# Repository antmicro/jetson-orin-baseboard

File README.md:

# Antmicro Baseboard for Jetson Orin

Copyright (c) 2022-2026 [Antmicro](https://www.antmicro.com)

## Overview

This project contains open hardware design files for a baseboard supporting [NVIDIA Jetson Orin series](https://www.nvidia.com/en-us/autonomous-machines/embedded-systems/jetson-orin/) of System on Modules (SoMs) including Jetson Orin NX and Jetson Orin Nano.
The board break-routes the typical I/O interfaces from the SoM.
Additionally, it exposes an expansion connector which allows it to be integrated with external processing modules using USB, PCIe or low-speed interfaces.

The design files were prepared in KiCad 9.x.

## Key features

* Two USB PD ports
* DC Power connector
* MIPI CSI-2 interfaces on 50-pin connectors with configurable lane mapping
* Micro HDMI connector
* USB-C 10 Gbps with USB PD and DP
* USB-C 10 Gbps
* USB-C UART with USB PD
* M.2 key M
* M.2 key E
* 1Gb Ethernet with PoE
* Custom expansion connector
* RTC battery backup

## Project structure

The main directory contains KiCad PCB project files, a LICENSE, and a README.
The remaining files are stored in the following directories:

* `img` - contains graphics for this README
* `doc` - contains [documentation and usage instructions](https://antmicro.github.io/jetson-orin-baseboard)

The board exposes MIPI CSI-2 interfaces using unified 50-pin connectors that are electrically compatible with a variety of video accessories created by Antmicro:

* [GMSL Deserializer](https://github.com/antmicro/gmsl-deserializer)
* [SDI-MIPI Video converter](https://github.com/antmicro/sdi-mipi-video-converter)
* [HDMI-MIPI bridge](https://github.com/antmicro/hdmi-mipi-bridge)
* [CVBS-MIPI bridge](https://github.com/antmicro/cvbs-mipi-bridge)
* [OV5640 Dual camera board](https://github.com/antmicro/ov5640-dual-camera-board)
* [OV9281 Dual camera board](https://github.com/antmicro/ov9281-camera-board)
* [Storage Expansion board](https://github.com/antmicro/job-storage-expansion)
* [FRAMOS camera adapter](https://github.com/antmicro/framos-csi-adapter)
* [Allied Vision Alvium Camera Adapter](https://github.com/antmicro/alvium-flexible-csi-adapter)

## Licensing

This project is published under the [Apache-2.0](LICENSE) license.

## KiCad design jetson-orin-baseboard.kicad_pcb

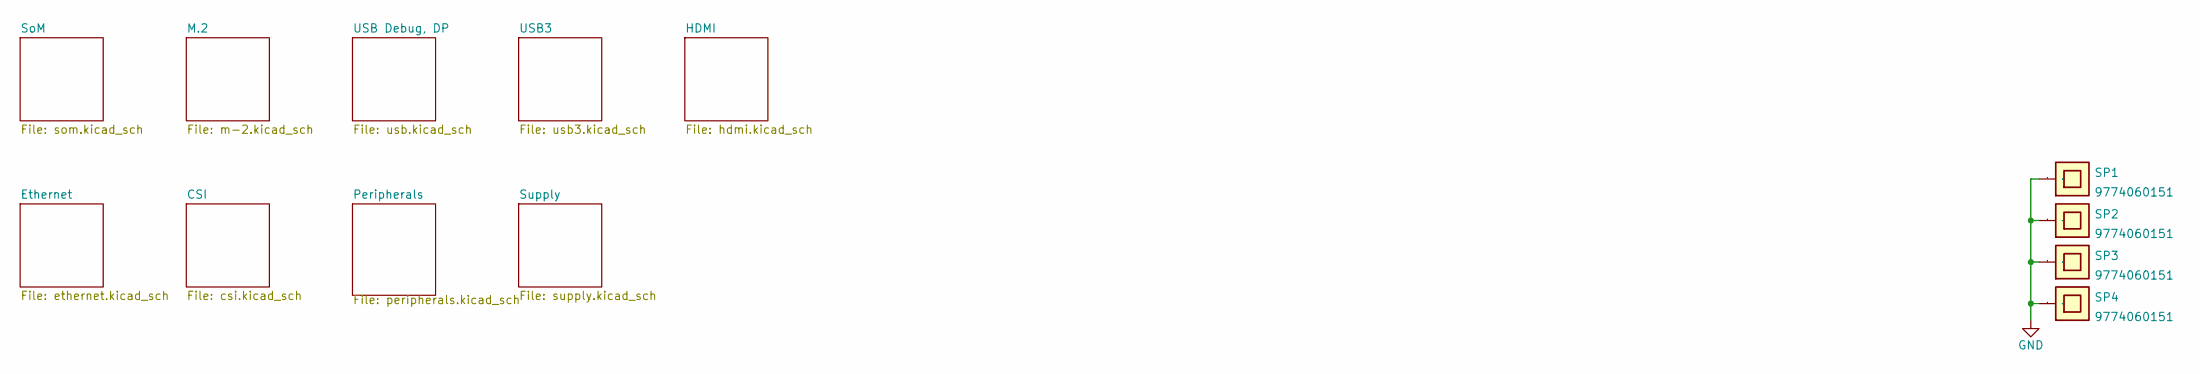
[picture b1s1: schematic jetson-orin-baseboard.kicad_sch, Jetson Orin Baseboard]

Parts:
SP1, SP2, SP3, SP4: 9774060151; MPN 9774060151

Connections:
GND: SP1.1, SP2.1, SP3.1, SP4.1; also elsewhere on the board

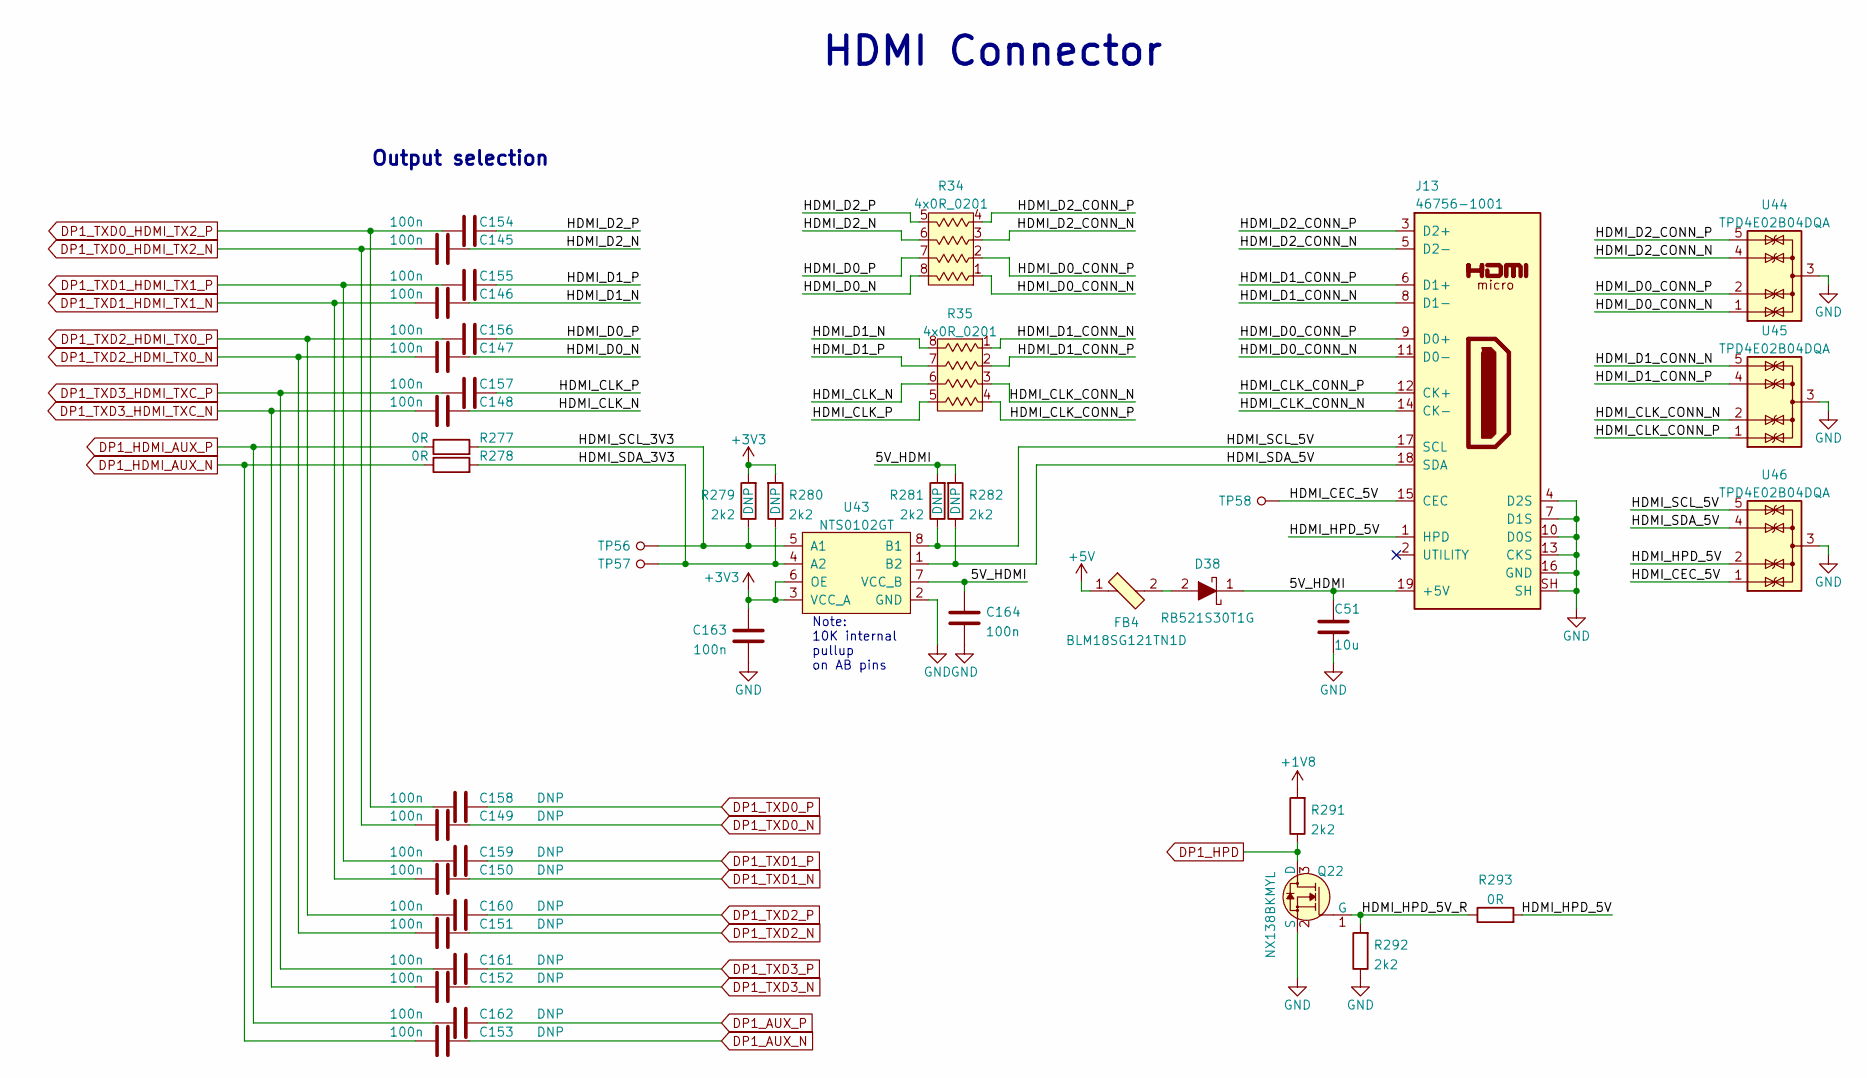
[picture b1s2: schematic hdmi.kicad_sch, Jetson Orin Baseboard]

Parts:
C51: C_10u_0603; 0603-cap; MPN GRM188R61A106KE69D
C145, C146, C147, C148, C149, C150, C151, C152, C153, C154, C155, C156, C157, C158, C159, C160, C161, C162, C163, C164: C_100n_0402; 0402-cap; MPN GRM155R61H104KE14D
D38: RB521S30T1G; SOD-523; MPN RB521S30T1G
FB4: BLM18SG121TN1D; 0603-res; MPN BLM18SG121TN1D
J13: 46756-1001; HDMI_Micro-D_Molex_46765-1x01; MPN 467651001
Q22: NX138BKMYL; DFN1006-3; MPN NX138BKMYL
R34, R35: 4x0R_0201_array; EXB18V; MPN EXB-18VR000X
R277, R278, R293: R_0R_0402; 0402-res; MPN ERJ2GE0R00X
R279, R280, R281, R282, R291, R292: R_2k2_0402; 0402-res; MPN RC0402FR-072K2L
TP56, TP57, TP58: TP_SMD_0_75MM; Testpoint_smd_0_75mm
U43: NTS0102GT; PSON50P100X195X50-8N; MPN NTS0102GT
U44, U45, U46: TPD4E02B04DQA; USON-10_2.5x1.0mm_P0.5mm; MPN TPD4E02B04DQAR

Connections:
+1V8: R291.2; also elsewhere on the board
+3V3: C163.2, R279.2, R280.2, U43.3 (VCC_A), U43.6 (OE); also elsewhere on the board
+5V: FB4.1; also elsewhere on the board
/HDMI/5V_HDMI: C51.1, C164.2, D38.1, J13.19 (+5V), R281.2, R282.2, U43.7 (VCC_B)
/HDMI/HDMI_CEC_5V: J13.15 (CEC), TP58.1, U46.1 (IO1), U46.10 (NC)
/HDMI/HDMI_CLK_CONN_N: J13.14 (CK-), R35.3, U45.2 (IO2), U45.9 (NC)
/HDMI/HDMI_CLK_CONN_P: J13.12 (CK+), R35.4, U45.1 (IO1), U45.10 (NC)
/HDMI/HDMI_CLK_N: C148.1, R35.6
/HDMI/HDMI_CLK_P: C157.1, R35.5
/HDMI/HDMI_D0_CONN_N: J13.11 (D0-), R34.1, U44.1 (IO1), U44.10 (NC)
/HDMI/HDMI_D0_CONN_P: J13.9 (D0+), R34.2, U44.2 (IO2), U44.9 (NC)
/HDMI/HDMI_D0_N: C147.1, R34.8
/HDMI/HDMI_D0_P: C156.1, R34.7
/HDMI/HDMI_D1_CONN_N: J13.8 (D1-), R35.1, U45.5 (IO4), U45.6 (NC)
/HDMI/HDMI_D1_CONN_P: J13.6 (D1+), R35.2, U45.4 (IO3), U45.7 (NC)
/HDMI/HDMI_D1_N: C146.1, R35.8
/HDMI/HDMI_D1_P: C155.1, R35.7
/HDMI/HDMI_D2_CONN_N: J13.5 (D2-), R34.3, U44.4 (IO3), U44.7 (NC)
/HDMI/HDMI_D2_CONN_P: J13.3 (D2+), R34.4, U44.5 (IO4), U44.6 (NC)
/HDMI/HDMI_D2_N: C145.1, R34.6
/HDMI/HDMI_D2_P: C154.1, R34.5
/HDMI/HDMI_HPD_5V: J13.1 (HPD), R293.2, U46.2 (IO2), U46.9 (NC)
/HDMI/HDMI_HPD_5V_R: Q22.1 (G), R292.2, R293.1
/HDMI/HDMI_SCL_3V3: R277.2, R279.1, TP56.1, U43.5 (A1)
/HDMI/HDMI_SCL_5V: J13.17 (SCL), R281.1, U43.8 (B1), U46.5 (IO4), U46.6 (NC)
/HDMI/HDMI_SDA_3V3: R278.2, R280.1, TP57.1, U43.4 (A2)
/HDMI/HDMI_SDA_5V: J13.18 (SDA), R282.1, U43.1 (B2), U46.4 (IO3), U46.7 (NC)
DP1_AUX_N: C153.1; also elsewhere on the board
DP1_AUX_P: C162.1; also elsewhere on the board
DP1_HDMI_AUX_N: C153.2, R278.1; also elsewhere on the board
DP1_HDMI_AUX_P: C162.2, R277.1; also elsewhere on the board
DP1_HPD: Q22.3 (D), R291.1; also elsewhere on the board
DP1_TXD0_HDMI_TX2_N: C145.2, C149.2; also elsewhere on the board
DP1_TXD0_HDMI_TX2_P: C154.2, C158.2; also elsewhere on the board
DP1_TXD0_N: C149.1; also elsewhere on the board
DP1_TXD0_P: C158.1; also elsewhere on the board
DP1_TXD1_HDMI_TX1_N: C146.2, C150.2; also elsewhere on the board
DP1_TXD1_HDMI_TX1_P: C155.2, C159.2; also elsewhere on the board
DP1_TXD1_N: C150.1; also elsewhere on the board
DP1_TXD1_P: C159.1; also elsewhere on the board
DP1_TXD2_HDMI_TX0_N: C147.2, C151.2; also elsewhere on the board
DP1_TXD2_HDMI_TX0_P: C156.2, C160.2; also elsewhere on the board
DP1_TXD2_N: C151.1; also elsewhere on the board
DP1_TXD2_P: C160.1; also elsewhere on the board
DP1_TXD3_HDMI_TXC_N: C148.2, C152.2; also elsewhere on the board
DP1_TXD3_HDMI_TXC_P: C157.2, C161.2; also elsewhere on the board
DP1_TXD3_N: C152.1; also elsewhere on the board
DP1_TXD3_P: C161.1; also elsewhere on the board
GND: C51.2, C163.1, C164.1, J13.4 (D2S), J13.7 (D1S), J13.10 (D0S), J13.13 (CKS), J13.16 (GND), J13.SH, Q22.2 (S), R292.1, U43.2 (GND), U44.3 (G), U44.8 (G), U45.3 (G), U45.8 (G), U46.3 (G), U46.8 (G); also elsewhere on the board
unnamed: D38.2, FB4.2

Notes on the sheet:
Output selection
Note: 10K internal pullup on AB pins
HDMI Connector

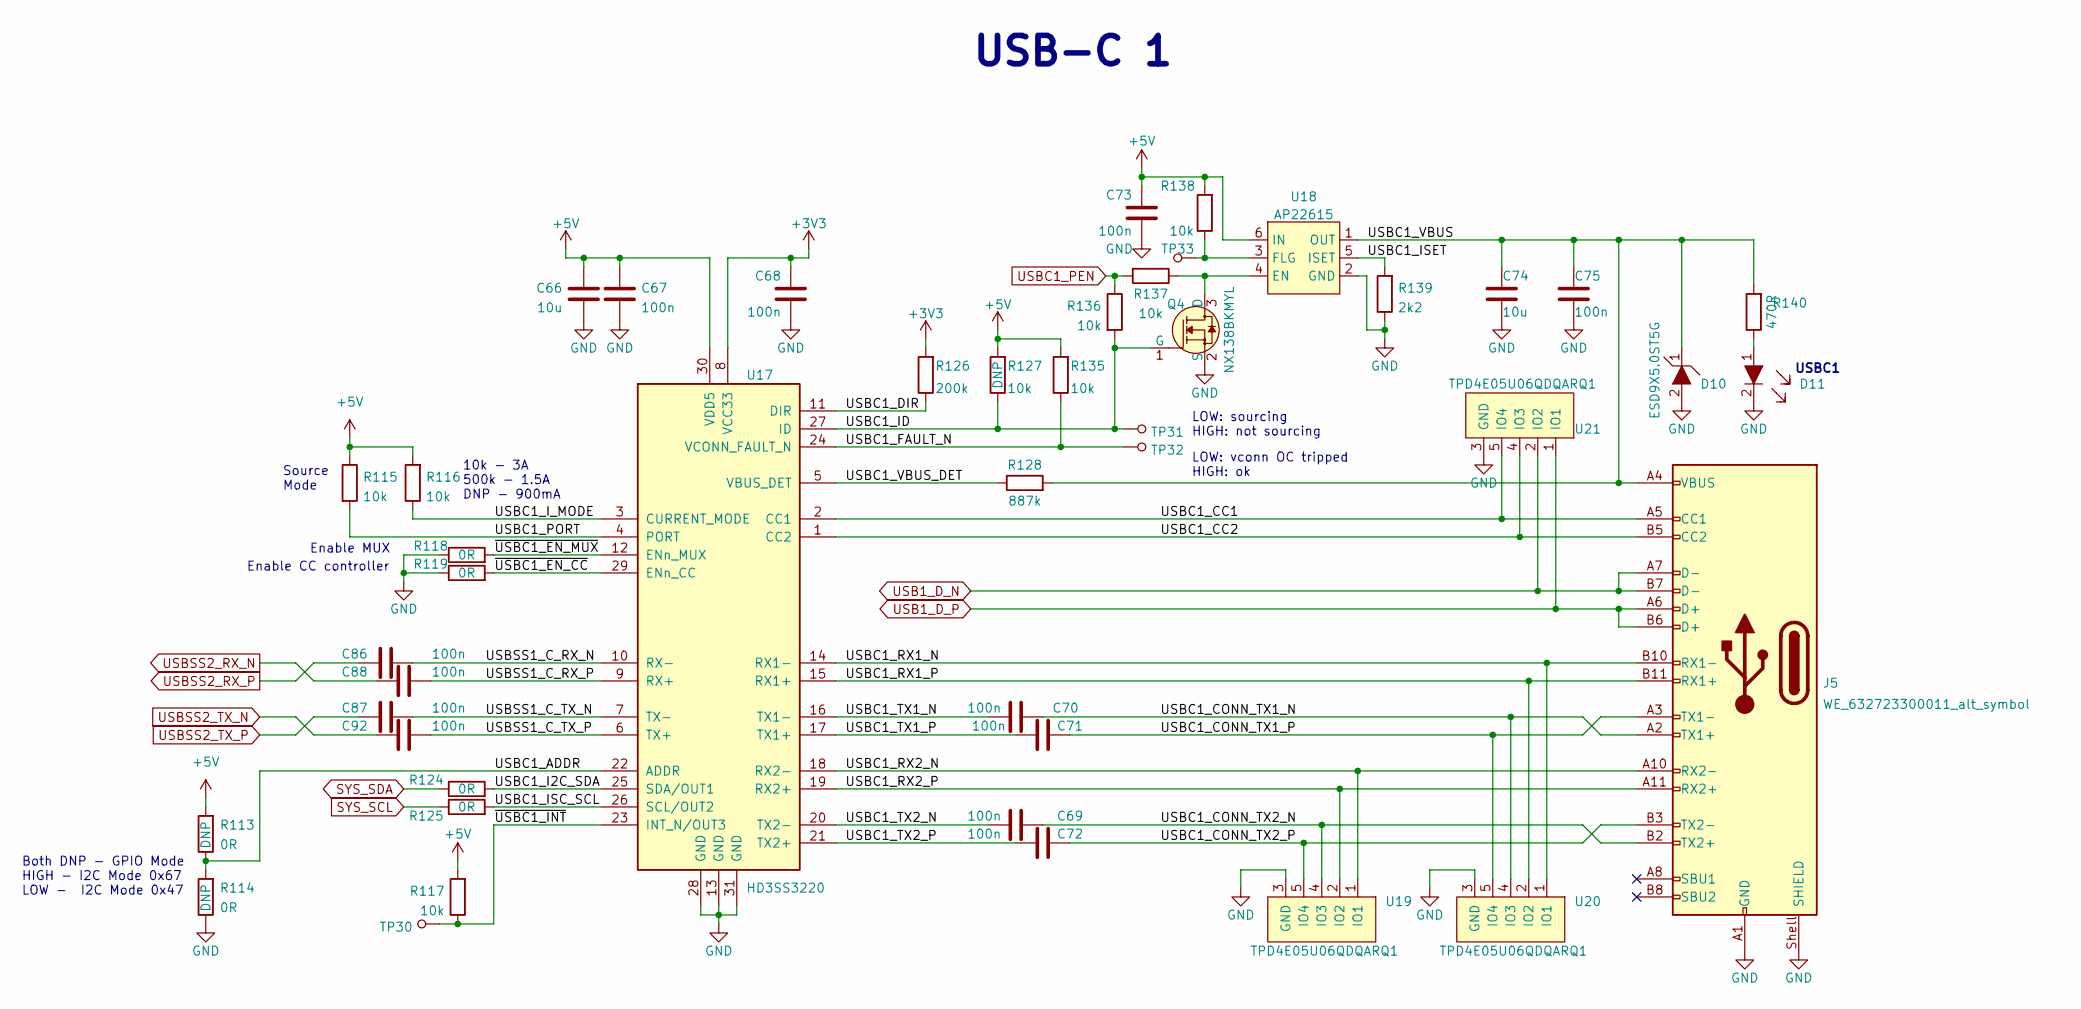
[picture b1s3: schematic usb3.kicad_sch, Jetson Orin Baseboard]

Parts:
C66, C74: C_10u_0603; 0603-cap; MPN GRM188R61A106KE69D
C67, C68, C69, C70, C71, C72, C73, C75, C86, C87, C88, C92: C_100n_0402; 0402-cap; MPN GRM155R61H104KE14D
D10: ESD9X5.0ST5G; SOD-923; MPN ESD9X5.0ST5G
D11: LTST-C190GKT; LED_0603; MPN LTST-C190GKT
J5: WE_632723300011_alt_symbol; WE_632723300011; MPN 632723300011
Q4: NX138BKMYL; DFN1006-3; MPN NX138BKMYL
R113, R114, R118, R119, R124, R125: R_0R_0402; 0402-res; MPN ERJ2GE0R00X
R115, R116, R117, R127, R135, R136, R137, R138: R_10k_0402; 0402-res; MPN CRCW040210K0FKEDHP
R126: R_200k_0402; 0402-res; MPN RC0402FR-07200KL
R128: R_887k_0402; 0402-res; MPN MCWR04X8870FTL
R139: R_2k2_0402; 0402-res; MPN RC0402FR-072K2L
R140: R_470R_0402; 0402-res; MPN CRCW0402470RFKED
TP30, TP31, TP32, TP33: TP_SMD_0_75MM; Testpoint_smd_0_75mm
U17: HD3SS3220; RNH0030A; MPN HD3SS3220RNHT
U18: AP22615; TSOT23-6; MPN AP22615AWU-7
U19, U20, U21: TPD4E05U06QDQARQ1; USON-10_2.5x1.0mm_P0.5mm; MPN TPD4E05U06QDQARQ1

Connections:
+3V3: C68.1, R126.2, U17.8 (VCC33); also elsewhere on the board
+5V: C66.1, C67.1, C73.1, R113.2, R115.1, R116.2, R117.2, R127.2, R135.2, R138.2, U17.30 (VDD5), U18.6 (IN); also elsewhere on the board
/USB3/USBC1_ADDR: R113.1, R114.2, U17.22 (ADDR)
/USB3/USBC1_CC1: J5.A5 (CC1), U17.2 (CC1), U21.5 (IO4), U21.6 (IO4)
/USB3/USBC1_CC2: J5.B5 (CC2), U17.1 (CC2), U21.4 (IO3), U21.7 (IO3)
/USB3/USBC1_CONN_TX1_N: C70.2, J5.A2 (TX1+), U20.4 (IO3), U20.7 (IO3)
/USB3/USBC1_CONN_TX1_P: C71.2, J5.A3 (TX1-), U20.5 (IO4), U20.6 (IO4)
/USB3/USBC1_CONN_TX2_N: C69.2, J5.B2 (TX2+), U19.4 (IO3), U19.7 (IO3)
/USB3/USBC1_CONN_TX2_P: C72.2, J5.B3 (TX2-), U19.5 (IO4), U19.6 (IO4)
/USB3/USBC1_DIR: R126.1, U17.11 (DIR)
/USB3/USBC1_FAULT_N: R135.1, TP32.1, U17.24 (VCONN_FAULT_N)
/USB3/USBC1_I2C_SDA: R124.2, U17.25 (SDA/OUT1)
/USB3/USBC1_ID: Q4.1 (G), R127.1, R136.2, TP31.1, U17.27 (ID)
/USB3/USBC1_ISC_SCL: R125.2, U17.26 (SCL/OUT2)
/USB3/USBC1_ISET: R139.2, U18.5 (ISET)
/USB3/USBC1_I_MODE: R116.1, U17.3 (CURRENT_MODE)
/USB3/USBC1_PORT: R115.2, U17.4 (PORT)
/USB3/USBC1_RX1_N: J5.B10 (RX1-), U17.14 (RX1-), U20.1 (IO1), U20.10 (IO1)
/USB3/USBC1_RX1_P: J5.B11 (RX1+), U17.15 (RX1+), U20.2 (IO2), U20.9 (IO2)
/USB3/USBC1_RX2_N: J5.A10 (RX2-), U17.18 (RX2-), U19.1 (IO1), U19.10 (IO1)
/USB3/USBC1_RX2_P: J5.A11 (RX2+), U17.19 (RX2+), U19.2 (IO2), U19.9 (IO2)
/USB3/USBC1_TX1_N: C70.1, U17.16 (TX1-)
/USB3/USBC1_TX1_P: C71.1, U17.17 (TX1+)
/USB3/USBC1_TX2_N: C69.1, U17.20 (TX2-)
/USB3/USBC1_TX2_P: C72.1, U17.21 (TX2+)
/USB3/USBC1_VBUS: C74.1, C75.1, D10.1, J5.A4 (VBUS), J5.A9 (VBUS), J5.B4 (VBUS), J5.B9 (VBUS), R128.2, R140.2, U18.1 (OUT)
/USB3/USBC1_VBUS_DET: R128.1, U17.5 (VBUS_DET)
/USB3/USBSS1_C_RX_N: C86.2, U17.10 (RX-)
/USB3/USBSS1_C_RX_P: C88.2, U17.9 (RX+)
/USB3/USBSS1_C_TX_N: C87.2, U17.7 (TX-)
/USB3/USBSS1_C_TX_P: C92.2, U17.6 (TX+)
/USB3/~USBC1_EN_CC: R119.2, U17.29 (ENn_CC)
/USB3/~USBC1_EN_MUX: R118.2, U17.12 (ENn_MUX)
/USB3/~USBC1_INT: R117.1, TP30.1, U17.23 (INT_N/OUT3)
GND: C66.2, C67.2, C68.2, C73.2, C74.2, C75.2, D10.2, D11.2, J5.A1 (GND), J5.A12 (GND), J5.B1 (GND), J5.B12 (GND), J5.Shell (SHIELD), Q4.2 (S), R114.1, R118.1, R119.1, R139.1, U17.13 (GND), U17.28 (GND), U17.31 (GND), U18.2 (GND), U19.3 (GND), U19.8 (GND), U20.3 (GND), U20.8 (GND), U21.3 (GND), U21.8 (GND); also elsewhere on the board
unnamed: D11.1, R140.1
unnamed: Q4.3 (D), R137.1, U18.4 (EN)
unnamed: R138.1, TP33.1, U18.3 (FLG)
SYS_SCL: R125.1; also elsewhere on the board
SYS_SDA: R124.1; also elsewhere on the board
USB1_D_N: J5.A7 (D-), J5.B7 (D-), U21.2 (IO2), U21.9 (IO2); also elsewhere on the board
USB1_D_P: J5.A6 (D+), J5.B6 (D+), U21.1 (IO1), U21.10 (IO1); also elsewhere on the board
USBC1_PEN: R136.1, R137.2; also elsewhere on the board
USBSS2_RX_N: C88.1; also elsewhere on the board
USBSS2_RX_P: C86.1; also elsewhere on the board
USBSS2_TX_N: C92.1; also elsewhere on the board
USBSS2_TX_P: C87.1; also elsewhere on the board

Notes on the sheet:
Source Mode
Enable MUX
Both DNP - GPIO Mode HIGH - I2C Mode 0x67 LOW - I2C Mode 0x47
USB-C 1
10k - 3A 500k - 1.5A DNP - 900mA
LOW: sourcing HIGH: not sourcing
USBC1
LOW: vconn OC tripped HIGH: ok
Enable CC controller

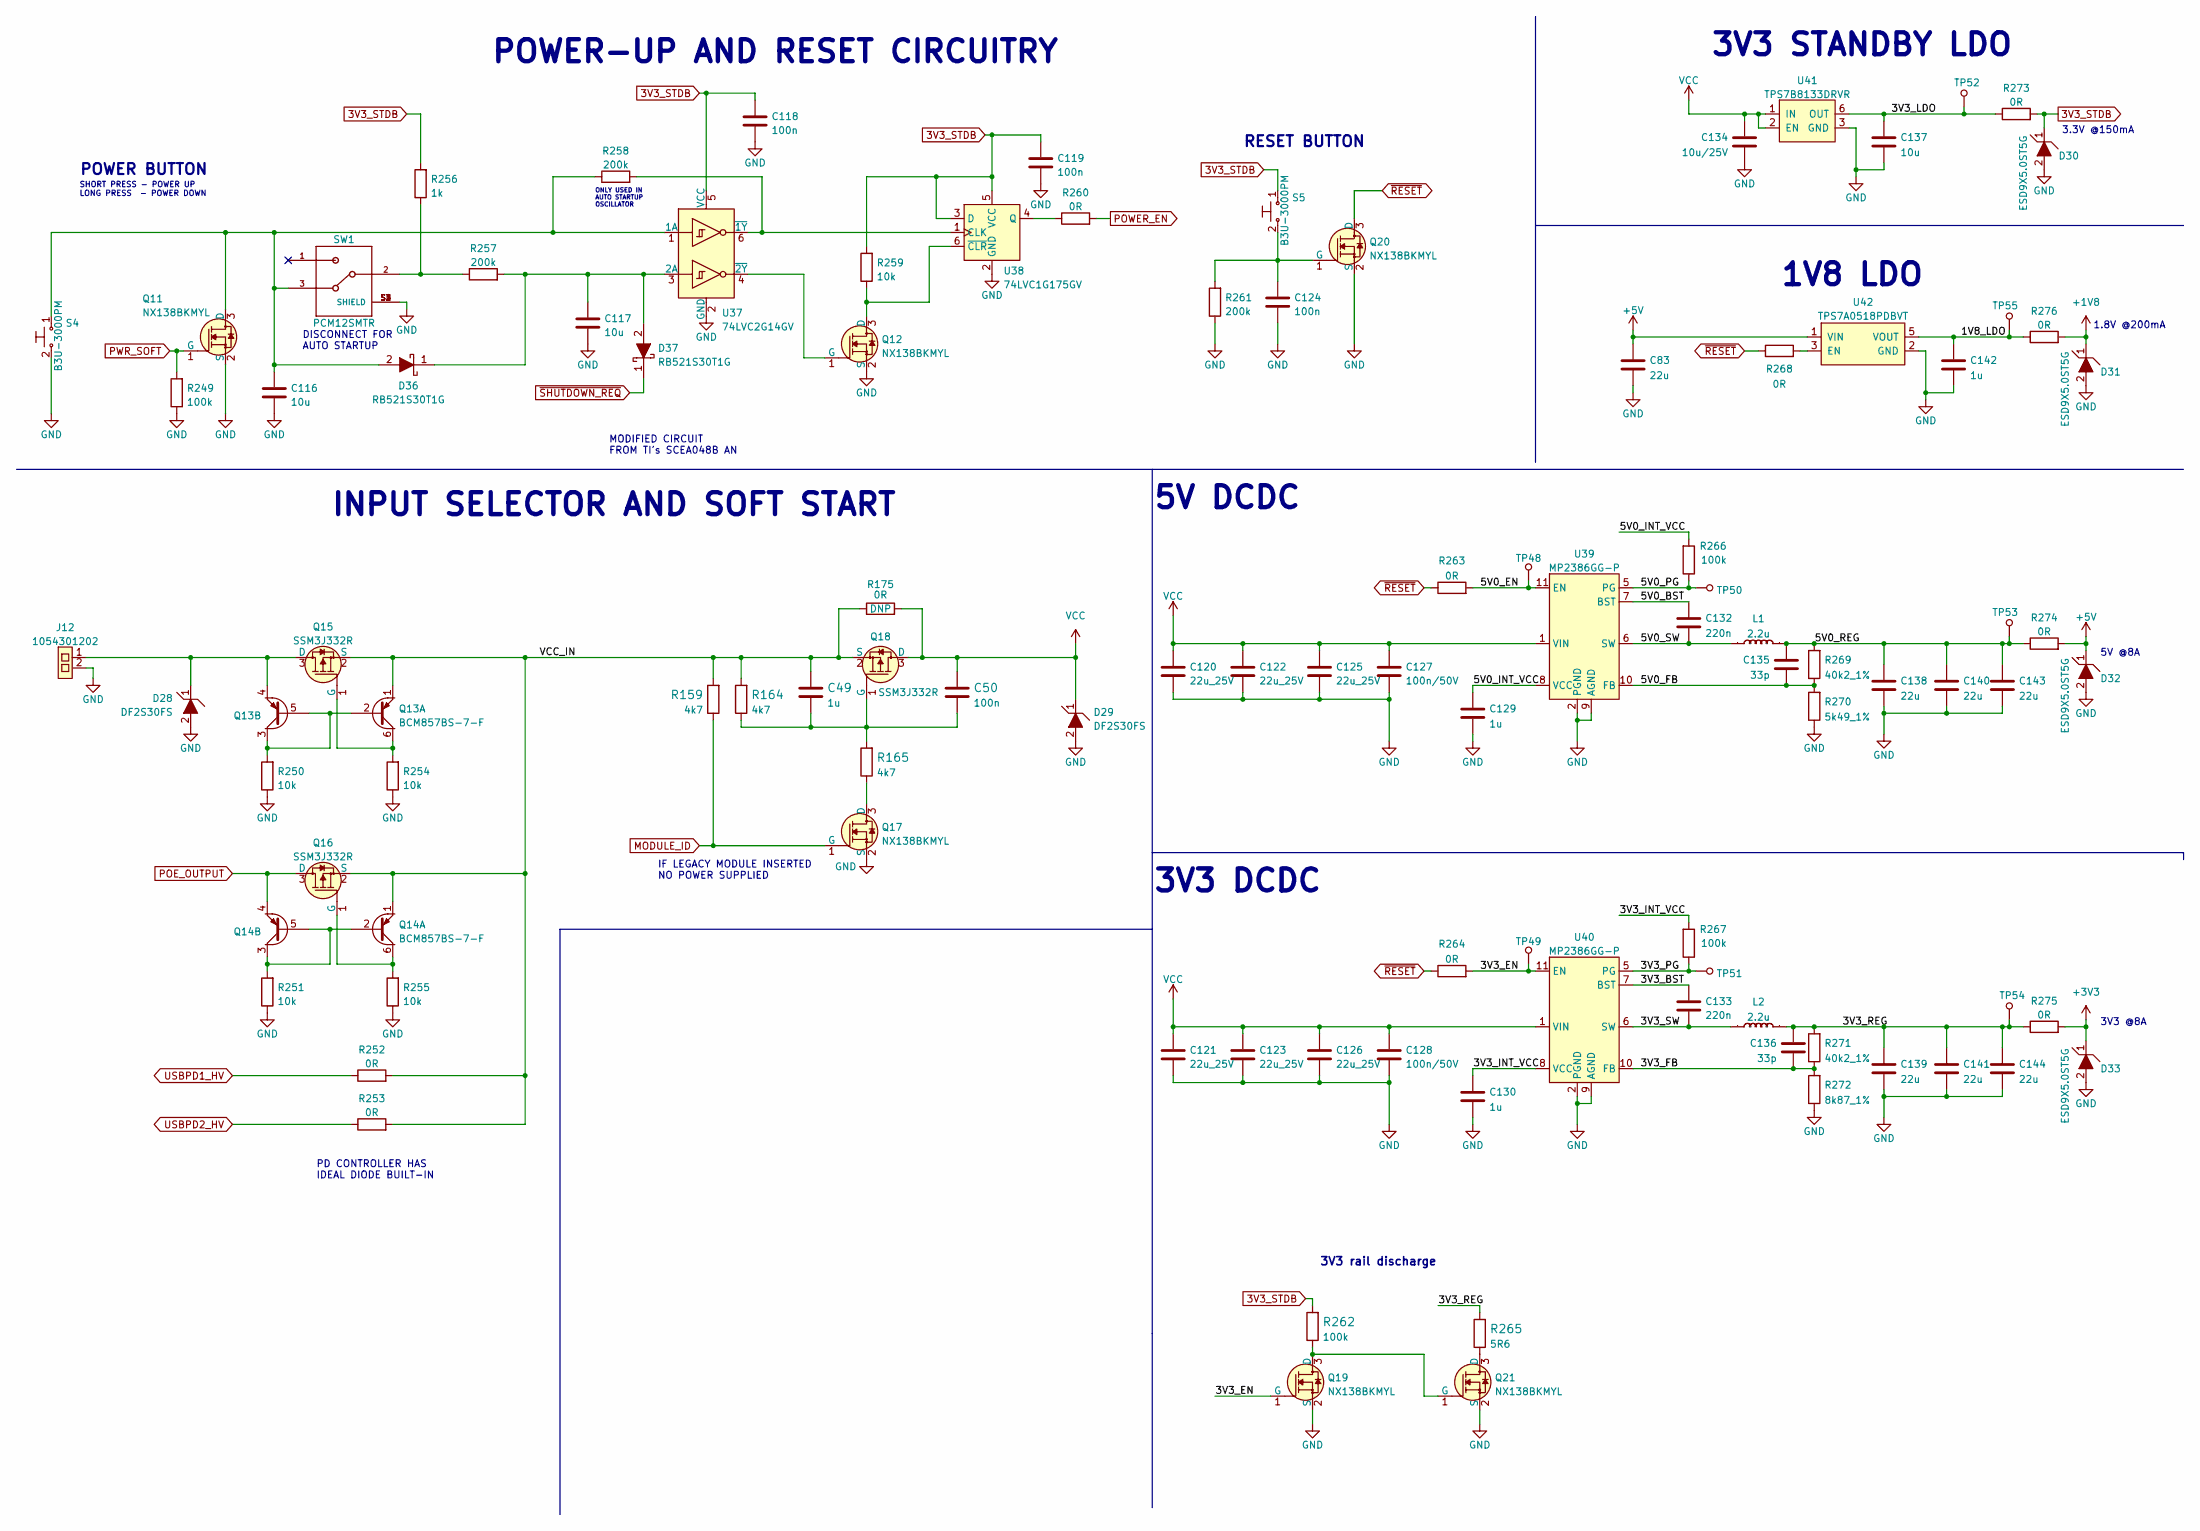
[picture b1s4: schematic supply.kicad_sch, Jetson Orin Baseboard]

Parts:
C49, C129, C130, C142: C_1u_0402; 0402-cap; MPN C1005X6S1A105K050BC
C50, C118, C119, C124: C_100n_0402; 0402-cap; MPN GRM155R61H104KE14D
C83, C138, C139, C140, C141, C143, C144: C_22u_0402; 0402-cap; MPN 04024W226MAT2A
C116, C117, C137: C_10u_0402; 0402-cap; MPN CC0402MRX5R5BB106
C120, C121, C122, C123, C125, C126: C_22u_0805_25V; 0805-cap; MPN CL21A226MAYNNNE
C127, C128: C_100n_0402_50V; 0402-cap; MPN GRM155R71H104KE14D
C132, C133: C_220n_0402; 0402-cap; MPN CC0402KRX5R6BB224
C134: C_10u_25V_0603; 0603-cap; MPN C1608X5R1E106M080AC
C135, C136: C_33p_0402; 0402-cap; MPN MC0402N330J500CT
D28, D29: DF2S30FS; SOD-923; MPN DF2S30FS
D30, D31, D32, D33: ESD9X5.0ST5G; SOD-923; MPN ESD9X5.0ST5G
D36, D37: RB521S30T1G; SOD-523; MPN RB521S30T1G
J12: Molex_Nano-Fit-105430_xx02-horizontal; Molex_Nano-Fit_105430-xx02_1x02_P2.50mm_Horizontal_SMD; MPN 1054301202
L1, L2: IHLP2525CZER2R2M01; IHLP2525CZER; MPN IHLP2525CZER8R2M01
Q11, Q12, Q17, Q19, Q20, Q21: NX138BKMYL; DFN1006-3; MPN NX138BKMYL
Q13, Q14: BCM857BS-7-F; SOT-363; MPN BCM857BS-7-F
Q15, Q16, Q18: SSM3J332R; SOT-23-3; MPN SSM3J332R,LF
R159, R164, R165: R_4k7_0402; 0402-res; MPN MCS04020C4701FE000
R175, R252, R253, R274, R275: R_0R_1206; 1206-res; MPN MCMR12X000_PTL
R249, R262, R266, R267: R_100k_0402; 0402-res; MPN CRCW0402100KFKEDHP
R250, R251, R254, R255, R259: R_10k_0402; 0402-res; MPN CRCW040210K0FKEDHP
R256: R_1k_0402; 0402-res; MPN CR0402-FX-1001GLF
R257, R258, R261: R_200k_0402; 0402-res; MPN RC0402FR-07200KL
R260, R263, R264, R268: R_0R_0402; 0402-res; MPN ERJ2GE0R00X
R265: R_5R6_0402; 0402-res; MPN ERJ2GEJ5R6X
R269, R271: R_40k2_1%_0402; 0402-res; MPN RC0402FR-0740K2L
R270: R_5k49_1%_0402; 0402-res; MPN ERJ-2RKF5491X
R272: R_8k87_1%_0402; 0402-res; MPN ERJ-2RKF8871X
R273, R276: R_0R_0603; 0603-res; MPN CR0603-J/-000ELF
S4, S5: B3U-3000PM; B3U-3000P; MPN B3U-3000PM
SW1: PCM12SMTR; MPN PCM13SMTR
TP48, TP49, TP50, TP51, TP52, TP53, TP54, TP55: TP_SMD_0_75MM; Testpoint_smd_0_75mm
U37: 74LVC2G14GV; SOT23-6L; MPN 74LVC2G14GV,125
U38: 74LVC1G175GV; SOT-23-6; MPN 74LVC1G175GV,125
U39, U40: MP2386GG-P; QFN-11_2x2mm_P0.5mm; MPN MP2386GG-P
U41: TPS7B8133DRVR; WSON6_TI_2x2mm; MPN TPS7B8133DRVR
U42: TPS7A0518PDBVT; SOT-23-5; MPN TPS7A0518PDBVT

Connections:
3V3_STDB: C118.1, C119.1, D30.1, R256.2, R259.2, R262.2, R273.2, S5.1, U37.5 (VCC), U38.3 (D), U38.5 (VCC); also elsewhere on the board
+1V8: D31.1, R276.2; also elsewhere on the board
+3V3: D33.1, R275.2; also elsewhere on the board
+5V: C83.1, D32.1, R274.2, U42.1 (VIN); also elsewhere on the board
/Supply/1V8_LDO: C142.1, R276.1, TP55.1, U42.5 (VOUT)
/Supply/3V3_BST: C133.1, U40.7 (BST)
/Supply/3V3_EN: Q19.1 (G), R264.2, TP49.1, U40.11 (EN)
/Supply/3V3_FB: C136.2, R271.1, R272.2, U40.10 (FB)
/Supply/3V3_INT_VCC: C130.1, R267.2, U40.8 (VCC)
/Supply/3V3_LDO: C137.1, R273.1, TP52.1, U41.6 (OUT)
/Supply/3V3_PG: R267.1, TP51.1, U40.5 (PG)
/Supply/3V3_REG: C136.1, C139.1, C141.1, C144.1, L2.2, R265.2, R271.2, R275.1, TP54.1
/Supply/3V3_SW: C133.2, L2.1, U40.6 (SW)
/Supply/5V0_BST: C132.2, U39.7 (BST)
/Supply/5V0_EN: R263.2, TP48.1, U39.11 (EN)
/Supply/5V0_FB: C135.2, R269.1, R270.2, U39.10 (FB)
/Supply/5V0_INT_VCC: C129.1, R266.2, U39.8 (VCC)
/Supply/5V0_PG: R266.1, TP50.1, U39.5 (PG)
/Supply/5V0_REG: C135.1, C138.1, C140.1, C143.1, L1.2, R269.2, R274.1, TP53.1
/Supply/5V0_SW: C132.1, L1.1, U39.6 (SW)
/Supply/VCC_IN: C49.1, Q13.1, Q14.1, Q15.2 (S), Q16.2 (S), Q18.2 (S), R159.2, R164.2, R175.1, R252.2, R253.2
GND: C83.2, C116.2, C117.2, C118.2, C119.2, C120.2, C121.2, C122.2, C123.2, C124.2, C125.2, C126.2, C127.2, C128.2, C129.2, C130.2, C134.2, C137.2, C138.2, C139.2, C140.2, C141.2, C142.2, C143.2, C144.2, D28.2, D29.2, D30.2, D31.2, D32.2, D33.2, J12.2, Q11.2 (S), Q12.2 (S), Q17.2 (S), Q19.2 (S), Q20.2 (S), Q21.2 (S), R249.1, R250.1, R251.1, R254.1, R255.1, R261.1, R270.1, R272.1, S4.2, SW1.S1 (SHIELD), SW1.S2 (SHIELD), SW1.S3 (SHIELD), SW1.S4 (SHIELD), U37.2 (GND), U38.2 (GND), U39.2 (PGND), U39.3 (PGND), U39.4 (PGND), U39.9 (AGND), U40.2 (PGND), U40.3 (PGND), U40.4 (PGND), U40.9 (AGND), U41.3 (GND), U41.4 (GND), U41.7 (GND), U42.2 (GND); also elsewhere on the board
MODULE_ID: Q17.1 (G), R159.1; also elsewhere on the board
unnamed: C49.2, C50.2, Q18.1 (G), R164.1, R165.2
unnamed: C116.1, D36.2, Q11.3 (D), R258.1, S4.1, SW1.3, U37.1 (1A)
unnamed: C117.1, D36.1, D37.2, R257.2, U37.3 (2A)
unnamed: C124.1, Q20.1 (G), R261.2, S5.2
unnamed: D28.1, J12.1, Q13.4, Q15.3 (D)
unnamed: Q12.1 (G), U37.4 (~2Y)
unnamed: Q12.3 (D), R259.1, U38.6 (~CLR)
unnamed: Q13.2, Q13.3, Q13.5, R250.2
unnamed: Q13.6, Q15.1 (G), R254.2
unnamed: Q14.2, Q14.3, Q14.5, R251.2
unnamed: Q14.6, Q16.1 (G), R255.2
unnamed: Q17.3 (D), R165.1
unnamed: Q19.3 (D), Q21.1 (G), R262.1
unnamed: Q21.3 (D), R265.1
unnamed: R256.1, R257.1, SW1.2
unnamed: R258.2, U37.6 (~1Y), U38.1 (CLK)
unnamed: R260.1, U38.4 (Q)
unnamed: R268.2, U42.3 (EN)
POE_OUTPUT: Q14.4, Q16.3 (D); also elsewhere on the board
POWER_EN: R260.2; also elsewhere on the board
PWR_SOFT: Q11.1 (G), R249.2; also elsewhere on the board
USBPD1_HV: R252.1; also elsewhere on the board
USBPD2_HV: R253.1; also elsewhere on the board
VCC: C50.1, C120.1, C121.1, C122.1, C123.1, C125.1, C126.1, C127.1, C128.1, C134.1, D29.1, Q18.3 (D), R175.2, U39.1 (VIN), U40.1 (VIN), U41.1 (IN), U41.2 (EN); also elsewhere on the board
~RESET: Q20.3 (D), R263.1, R264.1, R268.1; also elsewhere on the board
~SHUTDOWN_REQ: D37.1; also elsewhere on the board

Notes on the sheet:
ONLY USED IN AUTO STARTUP OSCILLATOR
5V @8A
3V3 STANDBY LDO
3.3V @150mA
MODIFIED CIRCUIT FROM TI's SCEA048B AN
1V8 LDO
SHORT PRESS - POWER UP LONG PRESS - POWER DOWN
5V DCDC
DISCONNECT FOR AUTO STARTUP
POWER BUTTON
POWER-UP AND RESET CIRCUITRY
3V3 @8A
3V3 DCDC
PD CONTROLLER HAS IDEAL DIODE BUILT-IN
INPUT SELECTOR AND SOFT START
IF LEGACY MODULE INSERTED NO POWER SUPPLIED
1.8V @200mA
3V3 rail discharge
RESET BUTTON

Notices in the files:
parts and their libraries:
License: MIT
